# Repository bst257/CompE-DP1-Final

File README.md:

# CompE-DP1-Final

Brief Specifications
	Basic Functionality:
	My add-on board is meant to be used as a form of input for the Raspberry Pi. It can read the values of four sliding potentiometers and return them as a value from 0 to 1023 and is meant to feature a system that can read a gesture input in one of four directions: up, down, left, or right.  However, the latter subsystem was unable to be implemented in time for the submission of the project.
	Power:
	My add-on board does not require a seperate power supply. The manual control subsystem only requires the 3.3V power that the Pi can supply and the gesture control system would be powered by the 5V power supply on the Pi. 
	Current:
	The ID EEPROM of the add-on board requires 1.7 mA of current, drawn from the 3.3V power supply of the Pi. The four potentiometers have a resistance of 10kΩ each so they draw 0.33 mA each for a total of 1.32 mA. The ADC IC used in the manual control system draws current on the order of µA. It is impossible to tell how much current would be drawn by the gesture control system without properly constructing it, as it would need to be measured with a multimeter.
	GPIO Pins/Communication buses:
	The add-on board uses BCM pins 0 and 1 for identification of the ID EEPROM.  The ADC IC of the manual control system uses SPI bus 0 and chip enable 0 so the same bus could be used with other chip enable lines.
	
Assembling and using the board
	https://i.imgur.com/OONl408.png
	I could not find a proper footprint for the sliders used in my project, but chose the footprint of another potentiometer to hold its place.

Installing and using the library
	Because I was only able to implement the manual control subsystem of my add-on board, my software library is rather simple.  It relies on the Adafuri_Python_GPIO and Adafruit_Python_MCP3008 libraries that can be obtained at https://github.com/adafruit/Adafruit_Python_GPIO and https://github.com/adafruit/Adafruit_Python_MCP3008 (It seems that as of yesterday the latter library is no longer supported, but it should still work for the purposes of this project).  The two function available for my project are detect_eeprom() which returns True if the hat is attached and False otherwise and read_sliders() which returns a list of the 4 values of the ADC as an integer in the range of 0-1023 based on the position of the sliders.

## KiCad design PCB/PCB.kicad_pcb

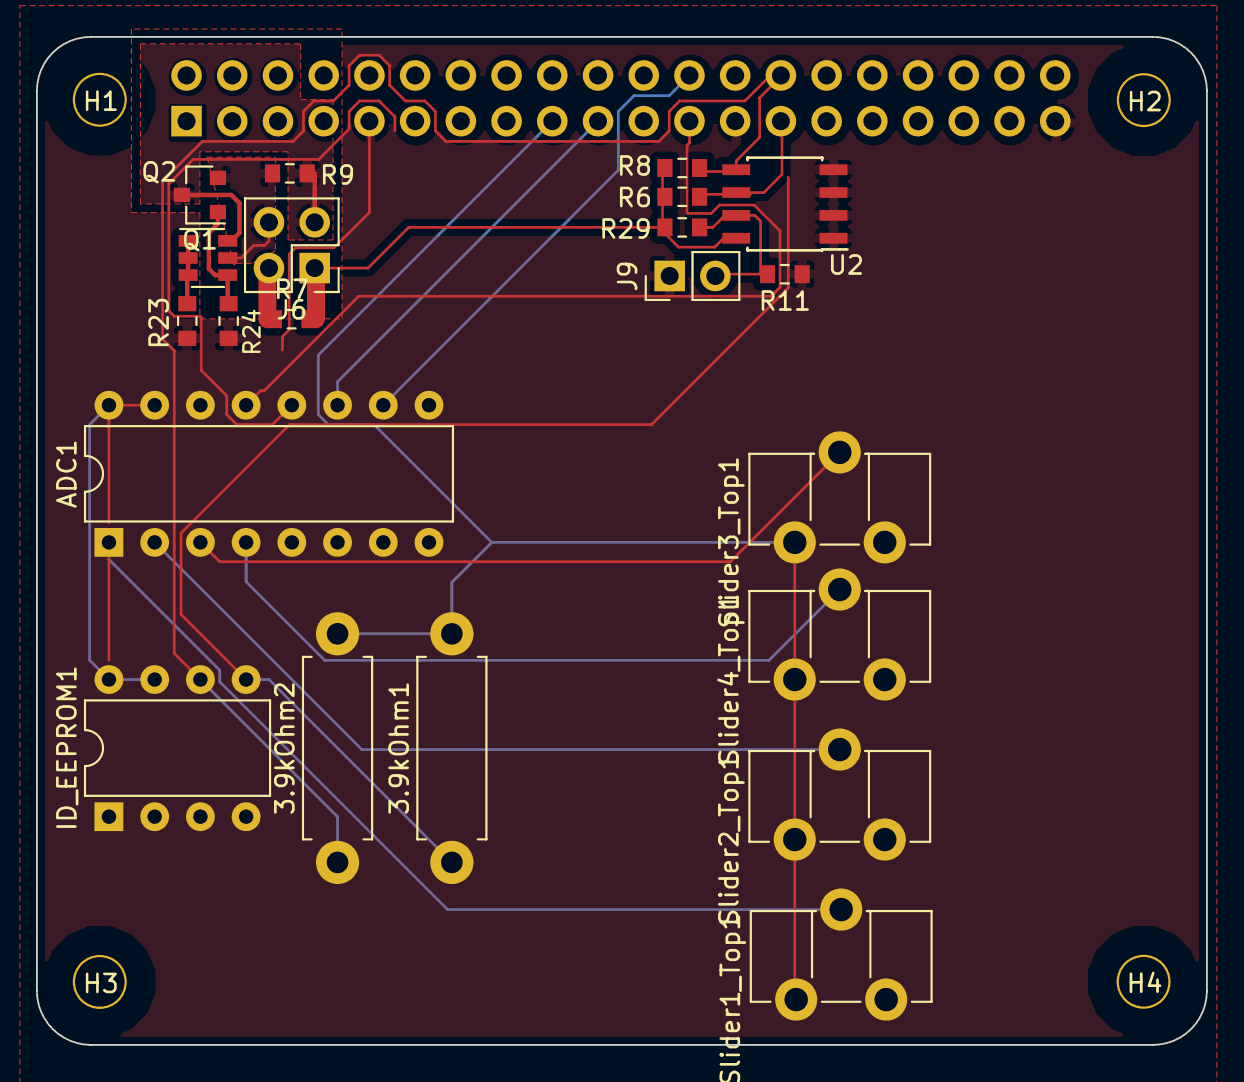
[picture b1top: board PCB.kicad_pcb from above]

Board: 4 copper layers, 65.0 x 56.0 mm, 26 parts (1 on the bottom side), 21 nets.

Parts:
3.9kOhm1, 3.9kOhm2: R_US; R_Axial_DIN0411_L9.9mm_D3.6mm_P12.70mm_Horizontal
ADC1: MCP3008; DIP-16_W7.62mm
H1, H2, H3, H4: 3mm_Mounting_Hole; NPTH_3mm_ID
ID_EEPROM1: 24LC32; DIP-8_W7.62mm
J6: CONN_02X02; PinHeader_2x02_P2.54mm_Vertical
J9: CONN_01X02; PinHeader_1x02_P2.54mm_Vertical
Pi1: Raspberry_Pi_2_3; PinSocket_2x20_P2.54mm_Vertical
Q1: DMG2305UX; SOT-23
Q2: DMMT5401; SOT-23-6
R6, R8: 3.9K; R_0603_1608Metric_Pad0.84x1.00mm_HandSolder
R7, R9, R11: DNP; R_0603_1608Metric_Pad0.84x1.00mm_HandSolder
R23, R24: 22; R_0603_1608Metric_Pad0.84x1.00mm_HandSolder
R29: 10K; R_0603_1608Metric_Pad0.84x1.00mm_HandSolder
Slider1_Top1, Slider2_Top1, Slider3_Top1, Slider4_Top1: R_Variable_US; Potentiometer_ACP_CA9-H5_Horizontal
U2: CAT24C32; SOIC-8_3.9x4.9mm_P1.27mm

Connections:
/ID_CLK: 3.9kOhm2.1, ID_EEPROM1.6, Pi1.28
/ID_Data: 3.9kOhm1.1, ID_EEPROM1.5, Pi1.27
/ID_SC_EEPROM: R8.2, U2.5
/ID_SD_EEPROM: R6.2, U2.6
/P3V3: J6.1, R6.1, R7.2, R8.1, R29.1, U2.8
/P3V3_HAT: J6.2, R7.1
/P5V: J6.3, Q1.3, Q2.6, R9.2
/P5V_HAT: J6.4, Q1.2, Q2.5, R9.1
/Pi_3.3V: 3.9kOhm1.2, 3.9kOhm2.2, ADC1.15, ADC1.16, ID_EEPROM1.7, ID_EEPROM1.8, Pi1.17, Slider1_Top1.1, Slider2_Top1.1, Slider3_Top1.1, Slider4_Top1.1
/SPI_CE: ADC1.10, Pi1.24
/SPI_CLK: ADC1.13, Pi1.23
/SPI_MISO: ADC1.12, Pi1.21
/SPI_MOSI: ADC1.11, Pi1.19
/Slider1_Wiper: ADC1.1, Slider1_Top1.2
/Slider2_Wiper: ADC1.2, Slider2_Top1.2
/Slider3_Wiper: ADC1.3, Slider3_Top1.2
/Slider4_Wiper: ADC1.4, Slider4_Top1.2
GND: ADC1.5, ADC1.6, ADC1.7, ADC1.8, ADC1.9, ADC1.14, ID_EEPROM1.4, J9.1, Pi1.39, R11.2, R23.2, R24.2, U2.1, U2.2, U2.3, U2.4
unnamed: J9.2, R11.1, R29.2, U2.7
unnamed: Q1.1, Q2.4, R24.1
unnamed: Q2.1, Q2.2, Q2.3, R23.1

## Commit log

2018-12-19 Fritzing Diagrams
2018-12-19 Python Code
2018-12-19 Library Fix
2018-12-22 Final Submission
2018-12-22 Corrected Screenshots PDF
